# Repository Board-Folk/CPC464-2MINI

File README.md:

# CPC464-2MINI

A Mini CPC464

** Forever Work In Progress **

A miniaturised version of Amstrad CPC464 second release with extensions. The main intention to try replace as much DIP with SMD as practically possible and have it as small as reasonably possible, with a standard board footprint that can later fit a 3D printed case that doesn't change between revisions. Latest versions, with everything on them, function as a 6128. This project is very much a private hobby project for now and is for fun and elements may lack any valid reason. It's been uploaded because of general interest.

More of the project may be dropped in here over time, kind of a place to sort out what's happened if you like, and what's working. There have been that many revisions/expansions it's been getting hard to keep track so it's nice to have a place. Things may be flagged as broken or untested where cautiously uploaded. 

## Revisions

The current version of the main board is v5.3, which uses the AMSGateArray Xilinx based gate array replacement linked to in the links section below. Thank you to all involved with that for this amazing project. Versions v4 and before require an original Amstrad 40010 or 40007 gate array (with adapter) for operation. Use of a 40007 somewhat impares operation especially regarding memory and other expansion compatiblity. Please see the readme file in each revisions folder for version specific information.

## Some Main Points

* Regulated 5V operation (centre terminal positive).
* The main board supports a full size original CPC464 Keyboard, **not** the later ones with the flat ribbon cables. An alternative PS/2 interface, which I expect most people will want to use is in the expansions folder.
* All releases still use 4164 RAM chips. Attempts at replacing these have so far failed due to the dual data bus (separate in and out pins are needed). Any help appreciated on this front, I can send schematics of my best guess so far which didn't work.
* All resistors and ceramic capacitors are 0805.
* Later revisions use PLCC32 instead of DIP28 for ROM due to space constraints.
* The v5 series board now also only supports the AY-3-8910 sound chip. Some earlier board supported the 8912, some both, the 8910 is much more readily available, also significantly cheaper. To note, you **can't** use an AY-3-8912 emulation board (well none that I've seen) with an Amstrad, they don't do the IO functions needed only sound.
* Some revisions of the board use a QFP44 Z80 not DIP40, including the latest revision, please check.
* Tape support changed for v5 on a different header needing an expansion card which hasn't been finished yet. Previous versions have a header compatible with the original 464 tape drive, and an adapter board for 3.5mm mono audio connections for a regular tape recorder/tapuino etc.
* There was a Mini-ITX version completed which included the disk interface (basically like a 6128), based on the pre-v5 boards in the Archive folder.
* As with original Amstrad CPCs of this generation, if you use the often more common A version AY-3-891x chip, e.g. AY-3-8910A you will need the SIP9 10K pullup resistor NR1 or your keyboard and joystick will not work correctly.
* All BOMs for now are just automatically generated iBOMs which only reflect the accuracy of the Kicad project they're from so be cautious.
* No, there's no HDMI port any of those other why didn't you things, feel free to add.

## Expansions

Expansion boards will be added over time. I'll try to place a big note in each readme which boards have not been tested. You'll probably want the Edge Connector, MINIDDI and PS/2 interfaces, but also check out the expansions folder.

Internal expansion boards stack vertically over a 2x25 pin header. Be warned, the rows for this are inverted from common secondary 6128 expansion cards that may already exist, though they typically need expansion adapter boards anyway for which there is one for this board. As things are at the moment each expansion card presents two headers for this to allow more options for stacking if you can't find the right socket/headers to stack directly. The primary expansions are:

* PS/2

An ATMEGA328/MT8816 based PS/2 adapter interface that mounts on the left of the board so you don't need an original keyboard.

* MINIEdge Edge Connector

It was decided that the main board wasn't going to include the original Amstrad edge connector as intended the expansions would be all neat and internal. The edge connector board solders on to the expansion connector on the base to provide the edge connector for traditional CPC expansions. This also has the virtue that the main board doesn't need ENIG, only this.

* MINIDDI

A version of the DDI-1 interface modified with the feelings of a 6128 and PPC640 to providing a 3.5" disk or Gotek drive interface. There's an adapter board for 3" drives.

** Check out the expansions folder for everything so far **

## Credits

Many thanks to Rob Taylor @peepouk and Chrissy @chris_jh with whom this project started, Richard Fry, Ian Stocks and the rest of the Board Folk Team. 
Special thanks to Noel Llopis for his amazing test ROM which has been invaluable for fixing buggy boards along the way.

## Links

  [AMSGateArray Gate Replacement Project](https://github.com/codedchip/AMSGateArray)<br>
  [Noel's Amstrad Diagnostics Test Suite](https://github.com/llopis/amstrad-diagnostics)

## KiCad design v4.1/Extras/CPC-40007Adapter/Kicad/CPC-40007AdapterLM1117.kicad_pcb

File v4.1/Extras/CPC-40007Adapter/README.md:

# CPC-40007Adapter

An adapter to plug an Amstrad 40007 Gate Array in to a 40010 Socket. It's not a great idea, but if you're stuck.

This is nothing to do with the CPC464-2MINI v5 board, which can't use an original gate array.

# Main points 

* There are many things fundamentally flawed in doing this, including broken addressing, for example it won't boot with a Dandanator and 128K.
* It might need long pins to get above other components on later CPC464-2MINI boards.
* Due to the old Ferranti process, this requires a second voltage and generates some heat.
* There might be some fundamental flaw that I've missed that causes bad things to happen.
* It uses an LM1117 instead of resistors for the second voltage required.

# BOM

iBOM can be found in BOM folder.

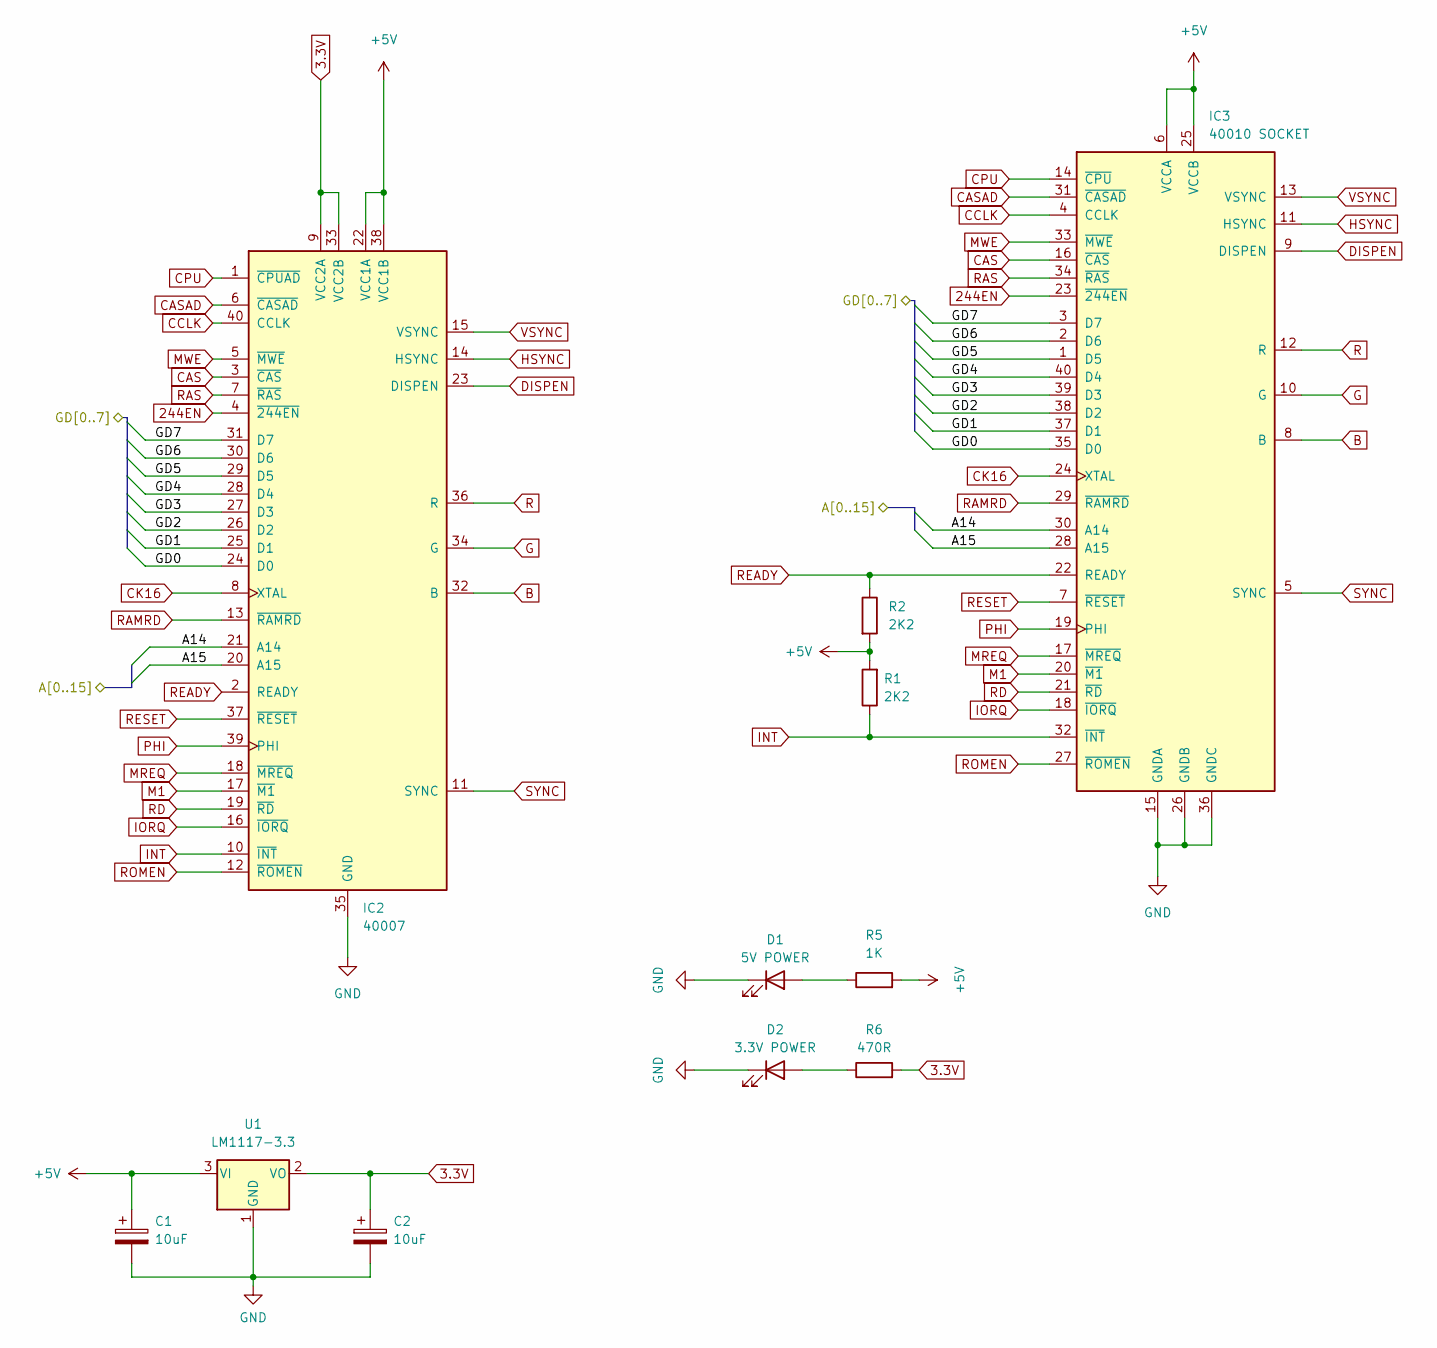
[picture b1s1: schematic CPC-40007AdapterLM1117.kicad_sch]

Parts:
C1, C2: 10uF; CP_EIA-3216-18_Kemet-A
D1: 5V POWER; LED_1206_3216Metric
D2: 3.3V POWER; LED_1206_3216Metric
IC2: 40007; DIP-40_W15.24mm_Socket_LongPads
IC3: 40010 SOCKET; 40010_Plug
R1, R2: 2K2; R_0805_2012Metric
R5: 1K; R_0805_2012Metric
R6: 470R; R_0805_2012Metric
U1: LM1117-3.3; SOT-223-3_TabPin2

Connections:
3.3V: C2.1, IC2.9 (VCC2A), IC2.33 (VCC2B), R6.2, U1.2 (VO)
244EN: IC2.4 (~244EN), IC3.23 (~244EN)
+5V: C1.1, IC2.22 (VCC1A), IC2.38 (VCC1B), IC3.6 (VCCA), IC3.25 (VCCB), R1.2, R2.2, R5.2, U1.3 (VI)
/A14: IC2.21 (A14), IC3.30 (A14)
/A15: IC2.20 (A15), IC3.28 (A15)
/GD0: IC2.24 (D0), IC3.35 (D0)
/GD1: IC2.25 (D1), IC3.37 (D1)
/GD2: IC2.26 (D2), IC3.38 (D2)
/GD3: IC2.27 (D3), IC3.39 (D3)
/GD4: IC2.28 (D4), IC3.40 (D4)
/GD5: IC2.29 (D5), IC3.1 (D5)
/GD6: IC2.30 (D6), IC3.2 (D6)
/GD7: IC2.31 (D7), IC3.3 (D7)
B: IC2.32 (B), IC3.8 (B)
CAS: IC2.3 (~CAS), IC3.16 (~CAS)
CASAD: IC2.6 (~CASAD), IC3.31 (~CASAD)
CCLK: IC2.40 (CCLK), IC3.4 (CCLK)
CK16: IC2.8 (XTAL), IC3.24 (XTAL)
CPU: IC2.1 (~CPUAD), IC3.14 (~CPU)
DISPEN: IC2.23 (DISPEN), IC3.9 (DISPEN)
G: IC2.34 (G), IC3.10 (G)
GND: C1.2, C2.2, D1.1 (K), D2.1 (K), IC2.35 (GND), IC3.15 (GNDA), IC3.26 (GNDB), IC3.36 (GNDC), U1.1 (GND)
HSYNC: IC2.14 (HSYNC), IC3.11 (HSYNC)
INT: IC2.10 (~INT), IC3.32 (~INT), R1.1
IORQ: IC2.16 (~IORQ), IC3.18 (~IORQ)
M1: IC2.17 (~M1), IC3.20 (~M1)
MREQ: IC2.18 (~MREQ), IC3.17 (~MREQ)
MWE: IC2.5 (~MWE), IC3.33 (~MWE)
unnamed: D1.2 (A), R5.1
unnamed: D2.2 (A), R6.1
PHI: IC2.39 (PHI), IC3.19 (PHI)
R: IC2.36 (R), IC3.12 (R)
RAMRD: IC2.13 (~RAMRD), IC3.29 (~RAMRD)
RAS: IC2.7 (~RAS), IC3.34 (~RAS)
RD: IC2.19 (~RD), IC3.21 (~RD)
READY: IC2.2 (READY), IC3.22 (READY), R2.1
RESET: IC2.37 (~RESET), IC3.7 (~RESET)
ROMEN: IC2.12 (~ROMEN), IC3.27 (~ROMEN)
SYNC: IC2.11 (SYNC), IC3.5 (SYNC)
VSYNC: IC2.15 (VSYNC), IC3.13 (VSYNC)

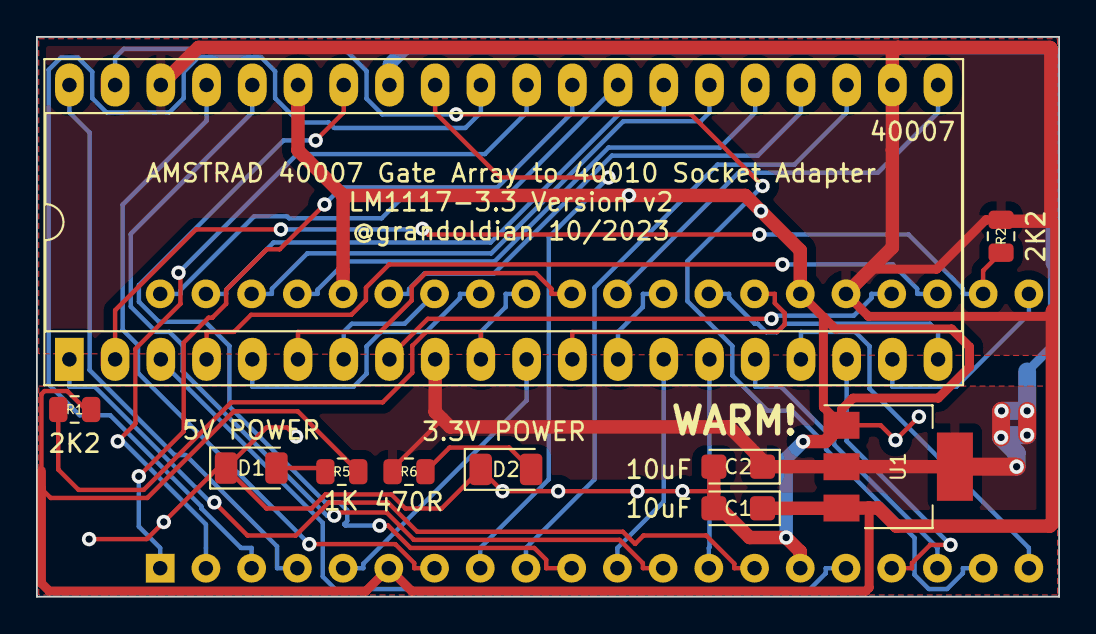
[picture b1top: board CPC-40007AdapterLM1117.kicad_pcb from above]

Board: 2 copper layers, 56.8 x 31.1 mm, 11 parts (0 on the bottom side), 40 nets.

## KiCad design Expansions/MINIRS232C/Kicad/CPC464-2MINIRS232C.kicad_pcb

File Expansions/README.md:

# CPC464-2MINI

CPC464-2MINI Expansions

* MINIEDGE

Edge connector for original expansion cards, for example the CPC Dandanator or whatever you might have.

* MINIPS/2

Atmega328 / MT8816 Based PS/2 Keyboard Adapter

* MINIDDI

3.5" Disk and Gotek Interface using the 765 disk controller and Epson SED. Standard PC floppy pinout. Adapter for 3" drives.

* MINIDOCK

Expansion to allow the installation of 6128 compatible expansion cards on the top of the system with additional 5V power injection.

* MINIRS232C

An updated version of the RS232C on a CPC464-2MINI Expansion board. Uses the MAX208 line driver / receiver with a 9 pin D-Sub instead

** On its way **

* MINIC2N

For the v5.3 board, a 9V system PSU and tape adapter to allow for the use of a Commodore C2N datasettes including both the C1530 and C1531 a well as 3.5mm Mic and Ear tape jacks for traditional cassette records and a header for an original CPC464 tape player as previously removed for v5. This works surprisingly well. Thanks to @PeepoUK for the idea.

** Untested and Unsorted **

* MINIUSIFACII

A USIFACII interface, though due to the chip shortage, this never got tested.

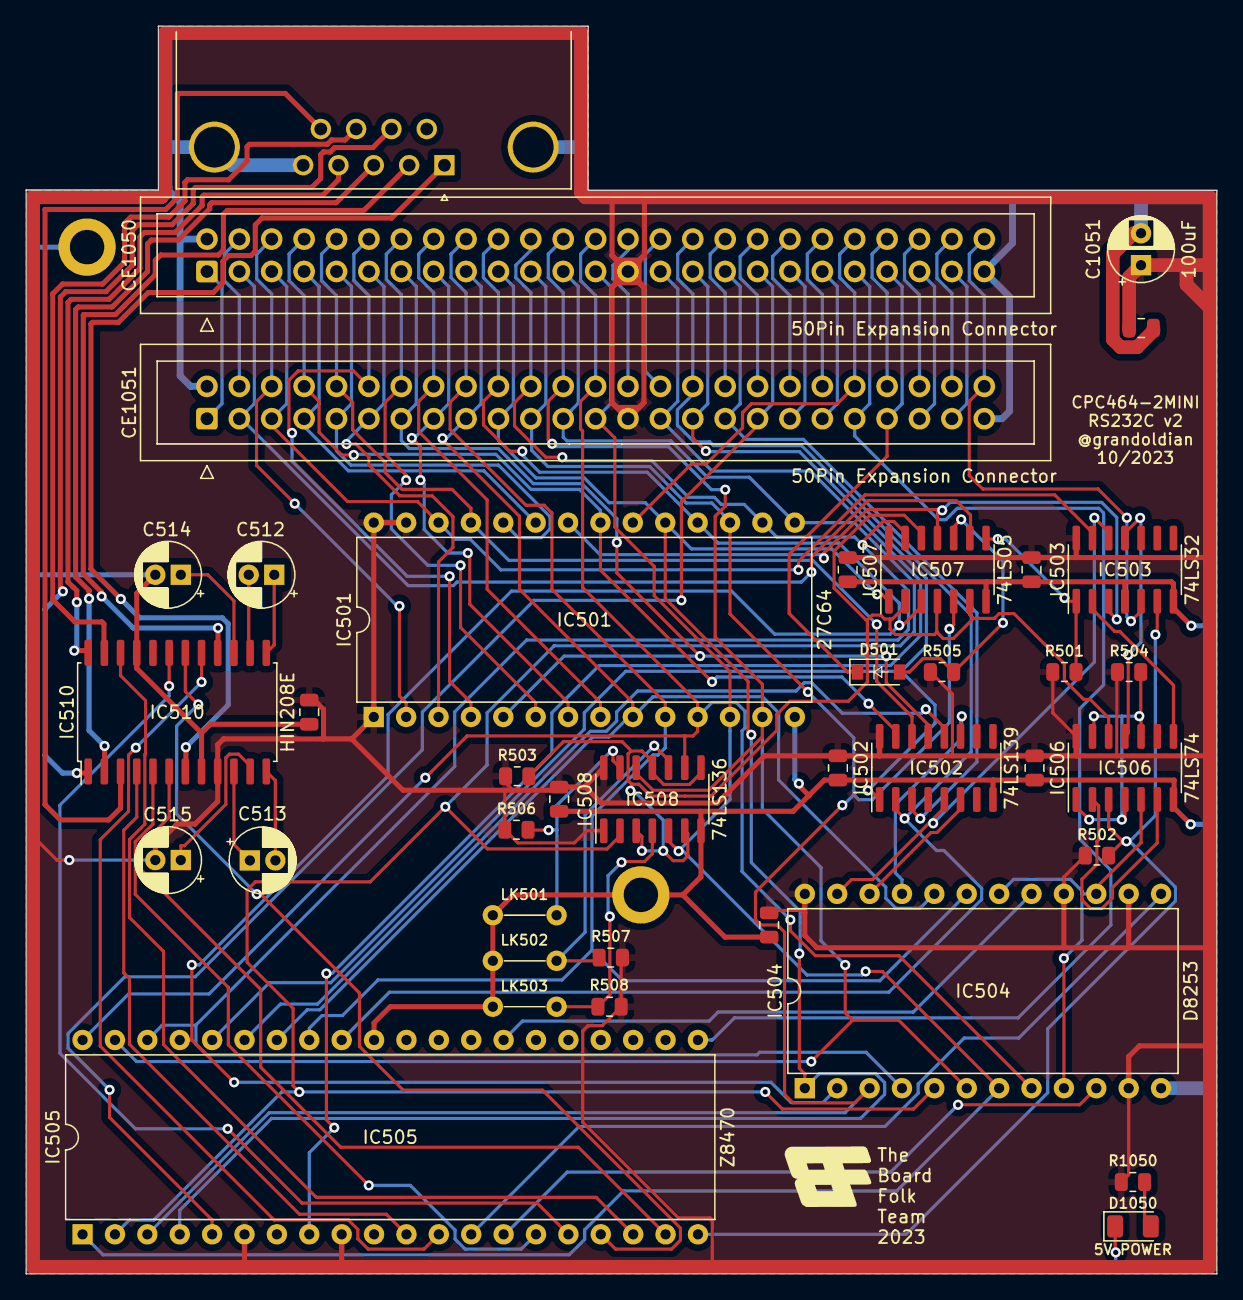
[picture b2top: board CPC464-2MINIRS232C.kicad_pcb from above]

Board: 2 copper layers, 93.4 x 97.9 mm, 42 parts (0 on the bottom side), 90 nets.

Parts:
C502, C503, C504, C505, C506, C507, C508, C1050: 100nF; C_0805_2012Metric
C512, C513, C514, C515: 0.1uF; CP_Radial_D5.0mm_P2.00mm
C1051: 100uF; CP_Radial_D5.0mm_P2.50mm
CE1050, CE1051: 50Pin Expansion Connector; EXPANSION_IDC_ANONYMISED
D501: 1N4148; D101
D1050: 5V POWER; LED_1206_3216Metric
G1: Board Folk Logo; BF8
H1, H7: MountingHole; MountingHole_2.7mm_M2.5_ISO14580_Pad
IC501: 27C64; DIP-28_W15.24mm
IC502: 74LS139; SOIC-16_3.9x9.9mm_P1.27mm
IC503: 74LS32; SOIC-14_3.9x8.7mm_P1.27mm
IC504: D8253; DIP-24_W15.24mm
IC505: Z8470; DIP-40_W15.24mm
IC506: 74LS74; SOIC-14_3.9x8.7mm_P1.27mm
IC507: 74LS05; SOIC-14_3.9x8.7mm_P1.27mm
IC508: 74LS136; SOIC-14_3.9x8.7mm_P1.27mm
IC510: HIN208E; SOIC-24W_7.5x15.4mm_P1.27mm
LK501, LK502, LK503: Capacitor
PL505: DB9; DSUB-9_Male_Horizontal_P2.77x2.84mm_EdgePinOffset7.70mm_Hou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
R501, R503, R504, R1050: 1K; R_0805_2012Metric
R502, R505: 670R; R_0805_2012Metric
R506, R507, R508: 10K; R_0805_2012Metric

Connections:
+5V: C502.1, C503.1, C504.1, C505.1, C506.1, C507.1, C508.1, C515.2, C1050.1, C1051.1, CE1050.27, CE1051.27, IC501.1 (VPP), IC501.27 (~PGM), IC501.28 (VCC), IC502.16 (VCC), IC503.14 (VCC), IC504.11 (GATE0), IC504.14 (GATE1), IC504.16 (GATE2), IC504.24 (VCC), IC505.6 (IEI), IC505.9 (VCC), IC506.14 (VCC), IC507.14 (VCC), IC508.1, IC508.14 (VCC), IC510.9 (VCC), R501.1, R502.1, R503.1, R504.1, R505.1, R506.1, R507.1, R508.1, R1050.2
/AMSRS232C SM Edited/A0: CE1050.18, CE1051.18, IC501.10 (A0), IC504.19 (A0), IC505.33 (C/~D)
/AMSRS232C SM Edited/A1: CE1050.17, CE1051.17, IC501.9 (A1), IC504.20 (A1), IC505.34 (B/~A)
/AMSRS232C SM Edited/A2: CE1050.16, CE1051.16, IC501.8 (A2)
/AMSRS232C SM Edited/A3: CE1050.15, CE1051.15, IC501.7 (A3)
/AMSRS232C SM Edited/A4: CE1050.14, CE1051.14, IC501.6 (A4)
/AMSRS232C SM Edited/A5: CE1050.13, CE1051.13, IC501.5 (A5), IC502.13 (A1)
/AMSRS232C SM Edited/A6: CE1050.12, CE1051.12, IC501.4 (A6)
/AMSRS232C SM Edited/A7: CE1050.11, CE1051.11, IC501.3 (A7)
/AMSRS232C SM Edited/A8: CE1050.10, CE1051.10, IC501.25 (A8), IC502.14 (A0)
/AMSRS232C SM Edited/A9: CE1050.9, CE1051.9, IC501.24 (A9)
/AMSRS232C SM Edited/A10: CE1050.8, CE1051.8, IC501.21 (A10), IC502.15 (E)
/AMSRS232C SM Edited/A11: CE1050.7, CE1051.7, IC501.23 (A11)
/AMSRS232C SM Edited/A12: CE1050.6, CE1051.6, IC501.2 (A12)
/AMSRS232C SM Edited/A13: CE1050.5, CE1051.5, IC501.26 (A13), IC503.13
/AMSRS232C SM Edited/A14: CE1050.4, CE1051.4
/AMSRS232C SM Edited/A15: CE1050.3, CE1051.3, IC507.9
/AMSRS232C SM Edited/CTS_IN: IC505.18 (~CTSA), IC510.22 (R3OUT)
/AMSRS232C SM Edited/D0: CE1050.26, CE1051.26, IC501.11 (D0), IC504.8 (D0), IC505.40 (D0), IC508.9
/AMSRS232C SM Edited/D1: CE1050.25, CE1051.25, IC501.12 (D1), IC504.7 (D1), IC505.1 (D1), IC508.5
/AMSRS232C SM Edited/D2: CE1050.24, CE1051.24, IC501.13 (D2), IC504.6 (D2), IC505.39 (D2), IC508.12
/AMSRS232C SM Edited/D3: CE1050.23, CE1051.23, IC501.15 (D3), IC504.5 (D3), IC505.2 (D3), IC508.2
/AMSRS232C SM Edited/D4: CE1050.22, CE1051.22, IC501.16 (D4), IC504.4 (D4), IC505.38 (D4), IC507.13
/AMSRS232C SM Edited/D5: CE1050.21, CE1051.21, IC501.17 (D5), IC504.3 (D5), IC505.3 (D5), IC507.5
/AMSRS232C SM Edited/D6: CE1050.20, CE1051.20, IC501.18 (D6), IC504.2 (D6), IC505.37 (D6), IC507.3
/AMSRS232C SM Edited/D7: CE1050.19, CE1051.19, IC501.19 (D7), IC504.1 (D7), IC505.4 (D7), IC507.1
/AMSRS232C SM Edited/DCD_IN: IC505.19 (~DCDA), IC510.6 (R1OUT)
/AMSRS232C SM Edited/DTR_OUT: IC505.16 (~DTRA), IC510.19 (T3IN)
/AMSRS232C SM Edited/RI_IN: IC505.11 (~RIA), IC510.4 (R2OUT)
/AMSRS232C SM Edited/RTS_OUT: IC505.17 (~RTSA), IC510.18 (T2IN)
/AMSRS232C SM Edited/RX_OUT: IC505.15 (TxDA), IC510.5 (T1IN)
/AMSRS232C SM Edited/TX_IN: IC505.12 (RxDA), IC510.17 (R4OUT)
A100: CE1050.50, CE1051.50, IC503.5
BUS: CE1050.40, CE1051.40
BUSAK: CE1050.38, CE1051.38
BUSRQ: CE1050.37, CE1051.37
CURSOR: CE1050.46, CE1051.46
DCLK: IC503.6, IC505.20 (CLK), IC506.3 (C), R502.2
DSEL: IC502.12 (O0), IC505.35 (~CE)
EXP: CE1050.48, CE1051.48
GND: C502.2, C503.2, C504.2, C505.2, C506.2, C507.2, C508.2, C514.2, C1050.2, C1051.2, CE1050.2, CE1050.49, CE1051.2, CE1051.49, D1050.1 (K), H1.1, H7.1, IC501.14 (GND), IC502.8 (GND), IC503.4, IC503.7 (GND), IC504.12 (GND), IC505.31 (GND), IC506.7 (GND), IC507.7 (GND), IC508.7 (GND), IC510.8 (GND), IC510.21 (T4IN), LK501.2, LK502.2, LK503.2, PL505.0 (PAD), PL505.5
HALT: CE1050.34, CE1051.34
INT: CE1050.35, CE1051.35, IC505.5 (~INT)
IORQ: CE1050.31, CE1051.31, IC502.1 (E), IC505.36 (~IORQ)
LPEN: CE1050.47, CE1051.47
M1: CE1050.29, CE1051.29, IC505.8 (~M1)
MREQ: CE1050.28, CE1051.28
NMI: CE1050.36, CE1051.36
unnamed: D501.2 (A), IC507.10, R505.2
unnamed: D1050.2 (A), R1050.1
unnamed: IC502.11 (O1), IC504.21 (~CS)
unnamed: IC503.1, IC507.8, R501.2
unnamed: IC504.9 (CLK0), IC504.15 (CLK1), IC504.18 (CLK2), IC506.5 (Q)
unnamed: IC504.10 (OUT0), IC505.14 (~TxCA)
unnamed: IC504.13 (OUT1), IC505.13 (~RxCA)
unnamed: IC504.17 (OUT2), IC505.27 (~RxTxCB)
unnamed: IC506.2 (D), IC506.6 (~Q)
unnamed: IC506.1 (~R), IC506.4 (~S), IC506.10 (~S), IC506.13 (~R), R504.2
unnamed: IC503.11, IC506.11 (C)
unnamed: IC503.2, IC506.8 (~Q)
unnamed: C513.1, IC510.10 (C1+)
unnamed: C513.2, IC510.12 (C1-)
unnamed: C512.1, IC510.13 (C2+)
unnamed: C512.2, IC510.14 (C2-)
unnamed: C515.1, IC510.11 (V+)
unnamed: C514.1, IC510.15 (V-)
unnamed: IC508.13, LK501.1, R506.2
unnamed: IC508.10, LK502.1, R507.2
unnamed: IC508.4, LK503.1, R508.2
ODDEN: IC506.12 (D), IC507.2, IC507.4, IC507.6, IC507.12, IC508.3, IC508.6, IC508.8, IC508.11, R503.2
RAMDIS: CE1050.45, CE1051.45
RAMRD: CE1050.44, CE1051.44
RD: CE1050.32, CE1051.32, IC502.2 (A0), IC505.32 (~RD)
READY: CE1050.39, CE1051.39
RESET: CE1050.41, CE1051.41, IC505.21 (~RESET)
RFSH: CE1050.30, CE1051.30
ROMDIS: CE1050.43, CE1051.43, D501.1 (K)
ROMEN: CE1050.42, CE1051.42, IC501.20 (~CE)
RS_CTS: IC510.23 (R3IN), PL505.8
RS_DCD: IC510.7 (R1IN), PL505.1
RS_DTR: IC510.24 (T3OUT), PL505.4
RS_RI: IC510.3 (R2IN), PL505.9
RS_RTS: IC510.1 (T2OUT), PL505.7
RS_RX: IC510.2 (T1OUT), PL505.3
RS_TX: IC510.16 (R4IN), PL505.2
SOUND: CE1050.1, CE1051.1
WR: CE1050.33, CE1051.33, IC502.3 (A1)
~RARD: IC502.6 (O2), IC504.22 (~RD)
~RAWR: IC502.5 (O1), IC503.12, IC504.23 (~WR)
~ROMOE: IC501.22 (~OE), IC503.3, IC507.11

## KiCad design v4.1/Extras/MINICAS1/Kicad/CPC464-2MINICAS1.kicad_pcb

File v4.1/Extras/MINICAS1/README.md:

# CPC464-2MINICAS1

Upper 64K Board for the CPC464-2MINI v4

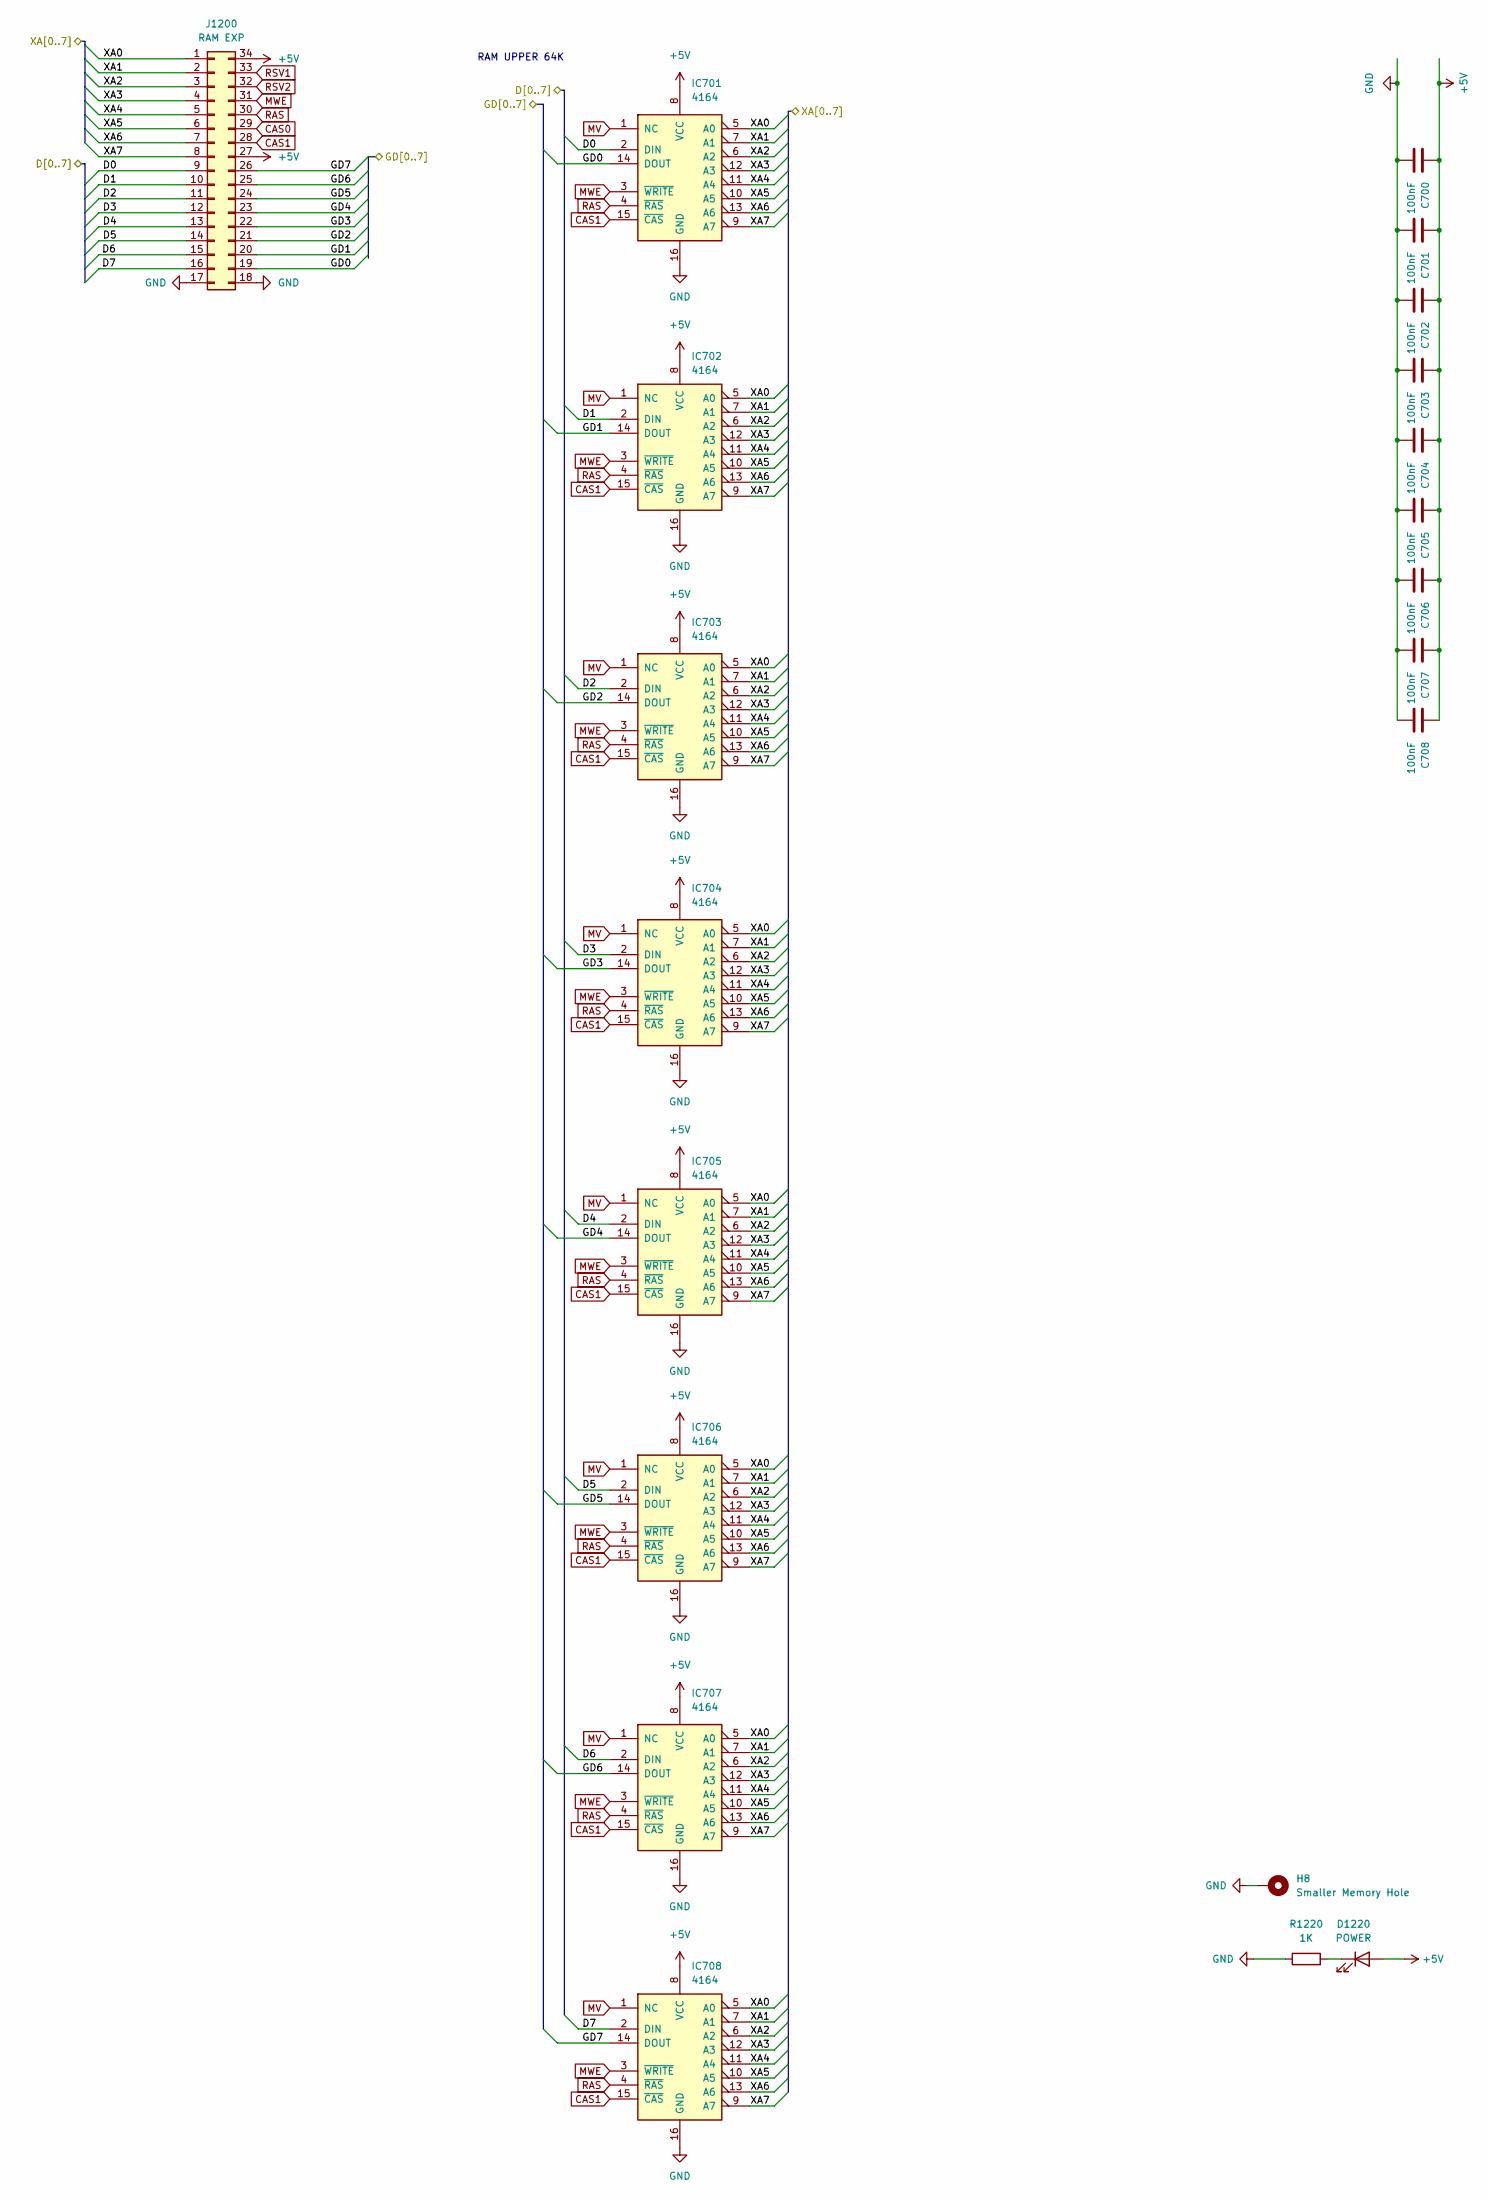
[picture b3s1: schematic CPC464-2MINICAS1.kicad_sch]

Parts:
C700, C701, C702, C703, C704, C705, C706, C707, C708: 100nF; C_0805_2012Metric; LCSC C49678
D1220: POWER; LED_1206_3216Metric
H8: Smaller Memory Hole; MountingHole_2.2mm_M2_DIN965_Pad
IC701, IC702, IC703, IC704, IC705, IC706, IC707, IC708: 4164; DIP-16_W7.62mm
J1200: RAM EXP; PinHeader_2x17_P2.54mm_Vertical
R1220: 1K; R_0805_2012Metric

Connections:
+5V: C700.1, C701.1, C702.1, C703.1, C704.1, C705.1, C706.1, C707.1, C708.1, D1220.2 (A), IC701.8 (VCC), IC702.8 (VCC), IC703.8 (VCC), IC704.8 (VCC), IC705.8 (VCC), IC706.8 (VCC), IC707.8 (VCC), IC708.8 (VCC), J1200.27, J1200.34
/D0: IC701.2 (DIN), J1200.9
/D1: IC702.2 (DIN), J1200.10
/D2: IC703.2 (DIN), J1200.11
/D3: IC704.2 (DIN), J1200.12
/D4: IC705.2 (DIN), J1200.13
/D5: IC706.2 (DIN), J1200.14
/D6: IC707.2 (DIN), J1200.15
/D7: IC708.2 (DIN), J1200.16
/GD0: IC701.14 (DOUT), J1200.19
/GD1: IC702.14 (DOUT), J1200.20
/GD2: IC703.14 (DOUT), J1200.21
/GD3: IC704.14 (DOUT), J1200.22
/GD4: IC705.14 (DOUT), J1200.23
/GD5: IC706.14 (DOUT), J1200.24
/GD6: IC707.14 (DOUT), J1200.25
/GD7: IC708.14 (DOUT), J1200.26
/XA0: IC701.5 (A0), IC702.5 (A0), IC703.5 (A0), IC704.5 (A0), IC705.5 (A0), IC706.5 (A0), IC707.5 (A0), IC708.5 (A0), J1200.1
/XA1: IC701.7 (A1), IC702.7 (A1), IC703.7 (A1), IC704.7 (A1), IC705.7 (A1), IC706.7 (A1), IC707.7 (A1), IC708.7 (A1), J1200.2
/XA2: IC701.6 (A2), IC702.6 (A2), IC703.6 (A2), IC704.6 (A2), IC705.6 (A2), IC706.6 (A2), IC707.6 (A2), IC708.6 (A2), J1200.3
/XA3: IC701.12 (A3), IC702.12 (A3), IC703.12 (A3), IC704.12 (A3), IC705.12 (A3), IC706.12 (A3), IC707.12 (A3), IC708.12 (A3), J1200.4
/XA4: IC701.11 (A4), IC702.11 (A4), IC703.11 (A4), IC704.11 (A4), IC705.11 (A4), IC706.11 (A4), IC707.11 (A4), IC708.11 (A4), J1200.5
/XA5: IC701.10 (A5), IC702.10 (A5), IC703.10 (A5), IC704.10 (A5), IC705.10 (A5), IC706.10 (A5), IC707.10 (A5), IC708.10 (A5), J1200.6
/XA6: IC701.13 (A6), IC702.13 (A6), IC703.13 (A6), IC704.13 (A6), IC705.13 (A6), IC706.13 (A6), IC707.13 (A6), IC708.13 (A6), J1200.7
/XA7: IC701.9 (A7), IC702.9 (A7), IC703.9 (A7), IC704.9 (A7), IC705.9 (A7), IC706.9 (A7), IC707.9 (A7), IC708.9 (A7), J1200.8
CAS0: J1200.29
CAS1: IC701.15 (~CAS), IC702.15 (~CAS), IC703.15 (~CAS), IC704.15 (~CAS), IC705.15 (~CAS), IC706.15 (~CAS), IC707.15 (~CAS), IC708.15 (~CAS), J1200.28
GND: C700.2, C701.2, C702.2, C703.2, C704.2, C705.2, C706.2, C707.2, C708.2, H8.1, IC701.16 (GND), IC702.16 (GND), IC703.16 (GND), IC704.16 (GND), IC705.16 (GND), IC706.16 (GND), IC707.16 (GND), IC708.16 (GND), J1200.17, J1200.18, R1220.1
MV: IC701.1 (NC), IC702.1 (NC), IC703.1 (NC), IC704.1 (NC), IC705.1 (NC), IC706.1 (NC), IC707.1 (NC), IC708.1 (NC)
MWE: IC701.3 (~WRITE), IC702.3 (~WRITE), IC703.3 (~WRITE), IC704.3 (~WRITE), IC705.3 (~WRITE), IC706.3 (~WRITE), IC707.3 (~WRITE), IC708.3 (~WRITE), J1200.31
unnamed: D1220.1 (K), R1220.2
RAS: IC701.4 (~RAS), IC702.4 (~RAS), IC703.4 (~RAS), IC704.4 (~RAS), IC705.4 (~RAS), IC706.4 (~RAS), IC707.4 (~RAS), IC708.4 (~RAS), J1200.30
RSV1: J1200.33
RSV2: J1200.32

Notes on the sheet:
RAM UPPER 64K

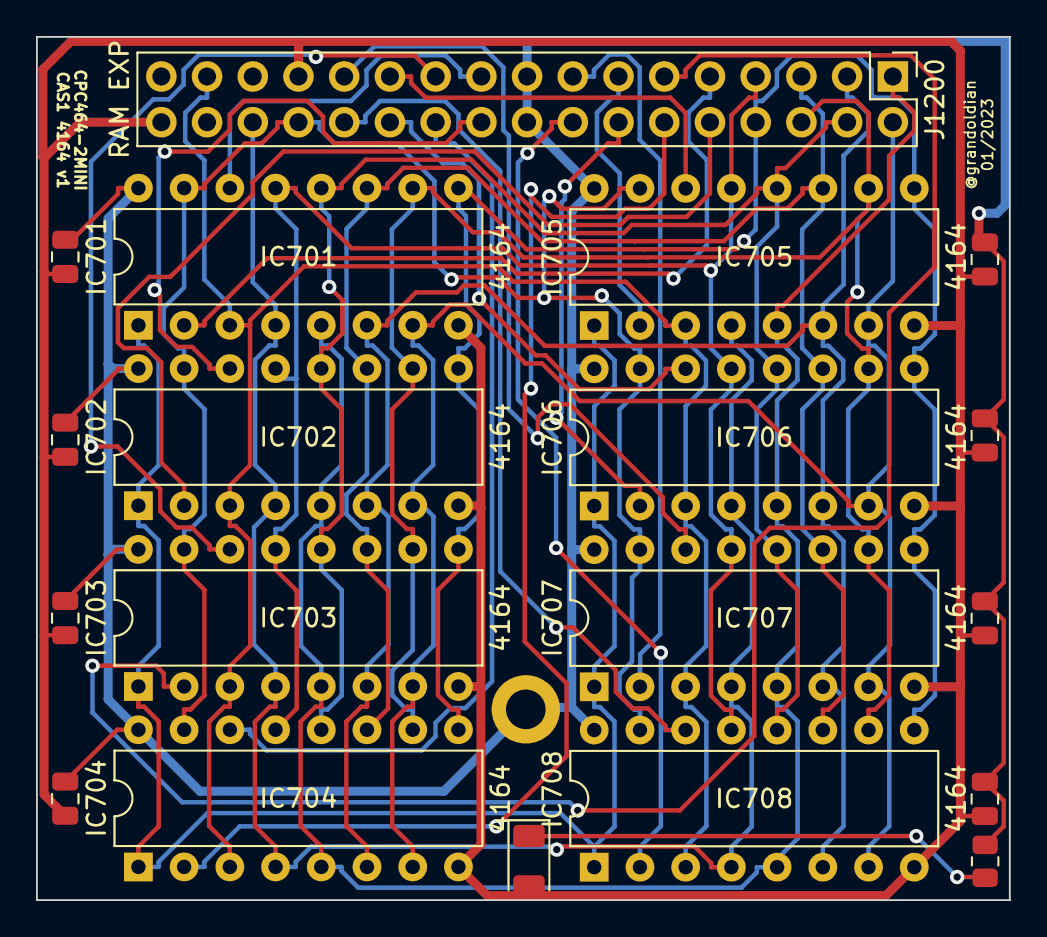
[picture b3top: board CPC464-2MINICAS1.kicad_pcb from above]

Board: 2 copper layers, 54.1 x 48.0 mm, 20 parts (0 on the bottom side), 31 nets.

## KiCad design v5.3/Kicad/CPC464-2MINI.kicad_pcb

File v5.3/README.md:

# CPC464-2MINI

CPC464-2MINI v5.3 Main Board

** Version 5 boards can't use an original Amstrad Gate array **

# Main points for this release

* AMSGateArray Xilinx based Gate Array. Needs skills.
* 128K RAM
* SMD 40031 GAL required for 128K operation
* QFP44 Z80 CPU
* AY-3-8910 Sound/IO Only
* PLCC32 ROM with switch selectable banking

# BOM

iBOM can be found in BOM folder.

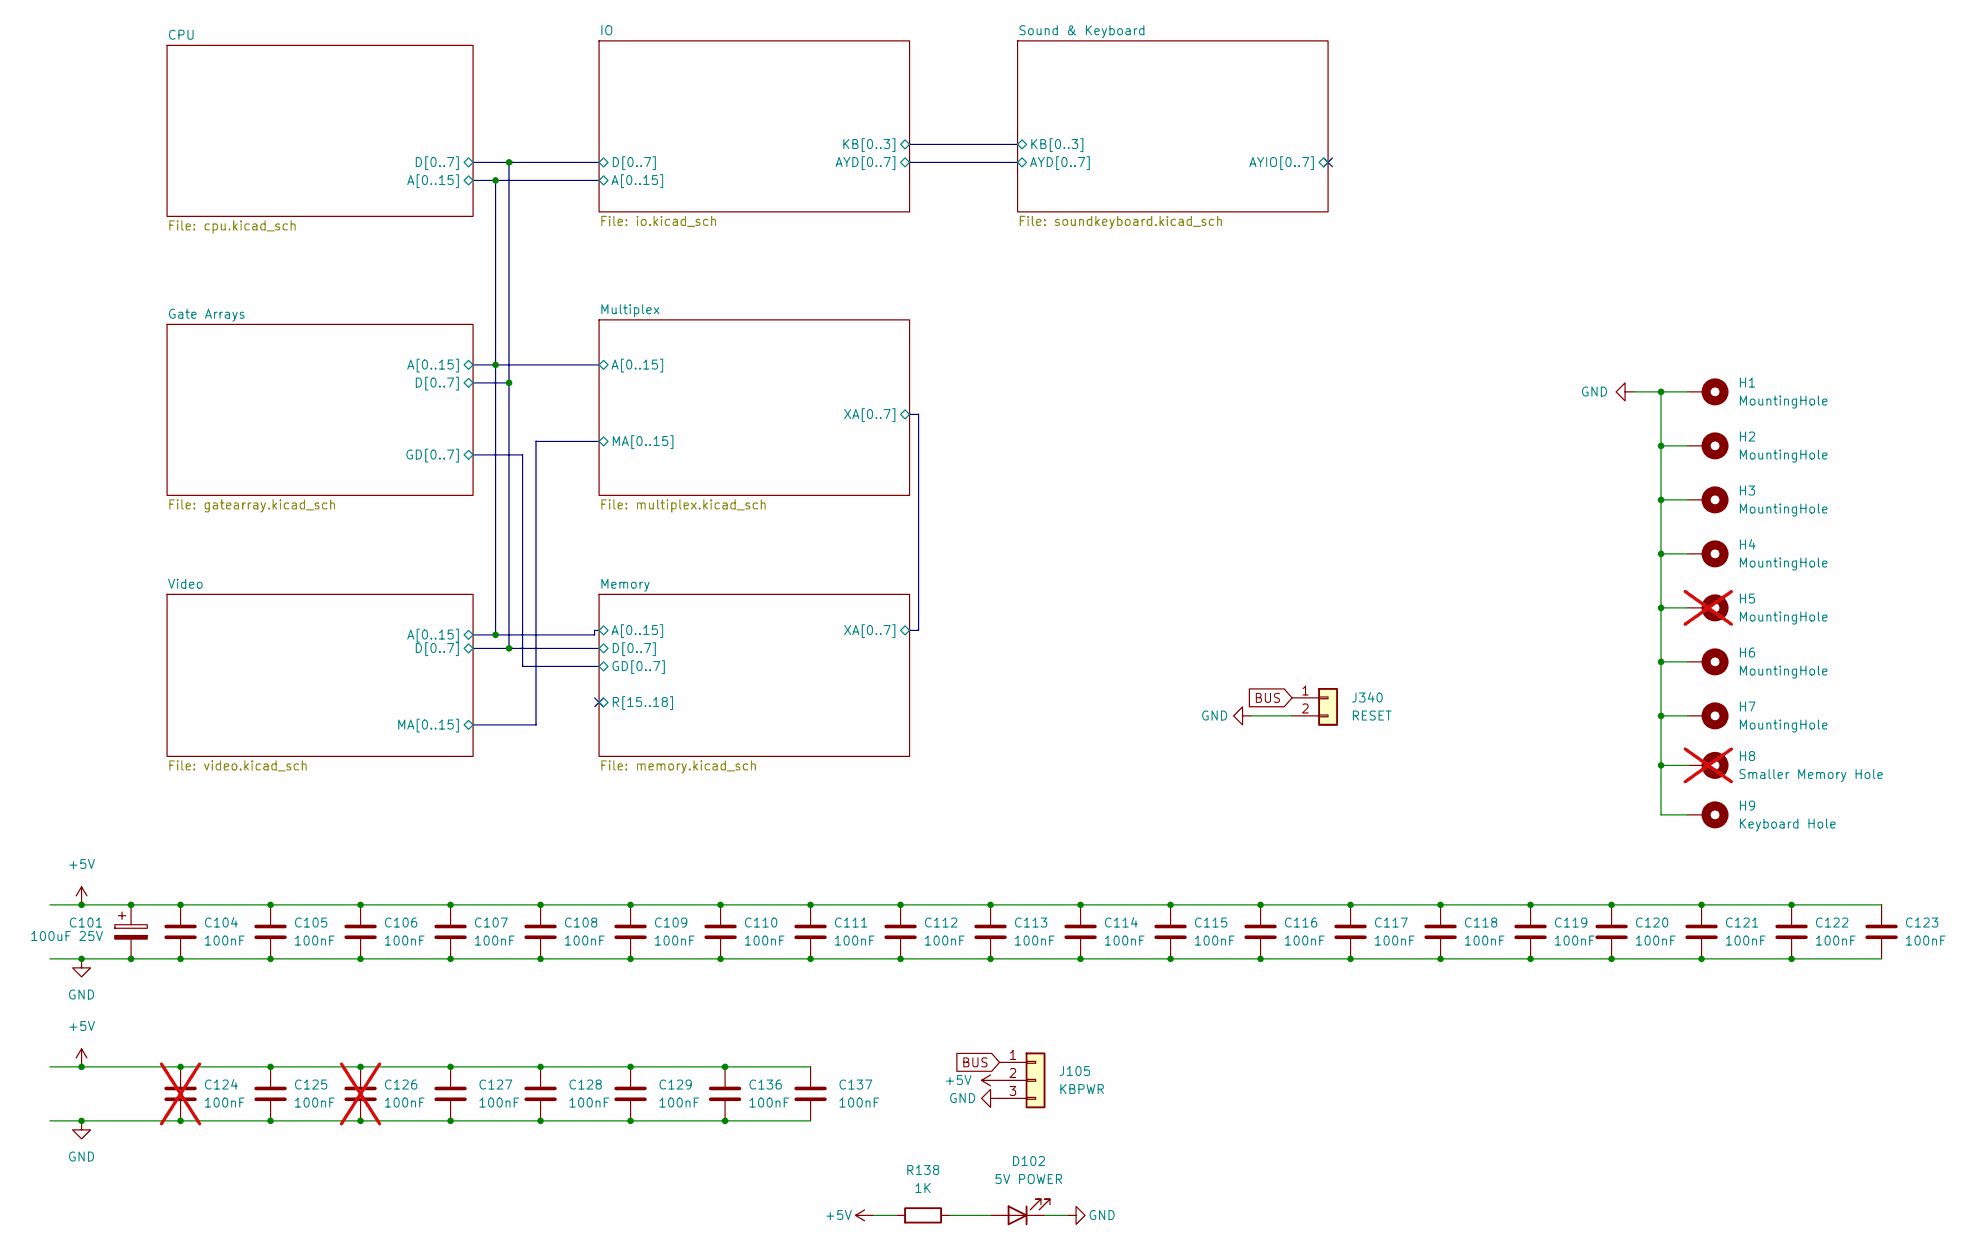
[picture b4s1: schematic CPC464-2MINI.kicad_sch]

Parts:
C101: 100uF 25V; CP_Radial_D5.0mm_P2.50mm
C104, C105, C106, C107, C108, C109, C110, C111, C112, C113, C114, C115, C116, C117, C118, C119, C120, C121, C122, C123, C125, C127, C128, C129, C136, C137: 100nF; C_0805_2012Metric; LCSC C49678
C124, C126: 100nF; C_0805_2012Metric; LCSC C49678; not fitted
D102: 5V POWER; LED_1206_3216Metric
H1, H2, H3, H4, H6, H7: MountingHole; MountingHole_2.7mm_M2.5_ISO14580_Pad
H5: MountingHole; MountingHole_2.7mm_M2.5_ISO14580_Pad; not fitted
H8: Smaller Memory Hole; MountingHole_2.2mm_M2_DIN965_Pad; not fitted
H9: Keyboard Hole; MountingHole_2.7mm_M2.5_ISO14580_Pad
J105: KBPWR; PinHeader_1x03_P2.54mm_Vertical
J340: RESET; PinHeader_1x02_P2.54mm_Vertical
R138: 1K; R_0805_2012Metric

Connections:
+5V: C101.1, C104.1, C105.1, C106.1, C107.1, C108.1, C109.1, C110.1, C111.1, C112.1, C113.1, C114.1, C115.1, C116.1, C117.1, C118.1, C119.1, C120.1, C121.1, C122.1, C123.1, C124.1, C125.1, C126.1, C127.1, C128.1, C129.1, C136.1, C137.1, J105.2, R138.2; also elsewhere on the board
BUS: J105.1, J340.1; also elsewhere on the board
GND: C101.2, C104.2, C105.2, C106.2, C107.2, C108.2, C109.2, C110.2, C111.2, C112.2, C113.2, C114.2, C115.2, C116.2, C117.2, C118.2, C119.2, C120.2, C121.2, C122.2, C123.2, C124.2, C125.2, C126.2, C127.2, C128.2, C129.2, C136.2, C137.2, D102.1 (K), H1.1, H2.1, H3.1, H4.1, H5.1, H6.1, H7.1, H8.1, H9.1, J105.3, J340.2; also elsewhere on the board
unnamed: D102.2 (A), R138.1
